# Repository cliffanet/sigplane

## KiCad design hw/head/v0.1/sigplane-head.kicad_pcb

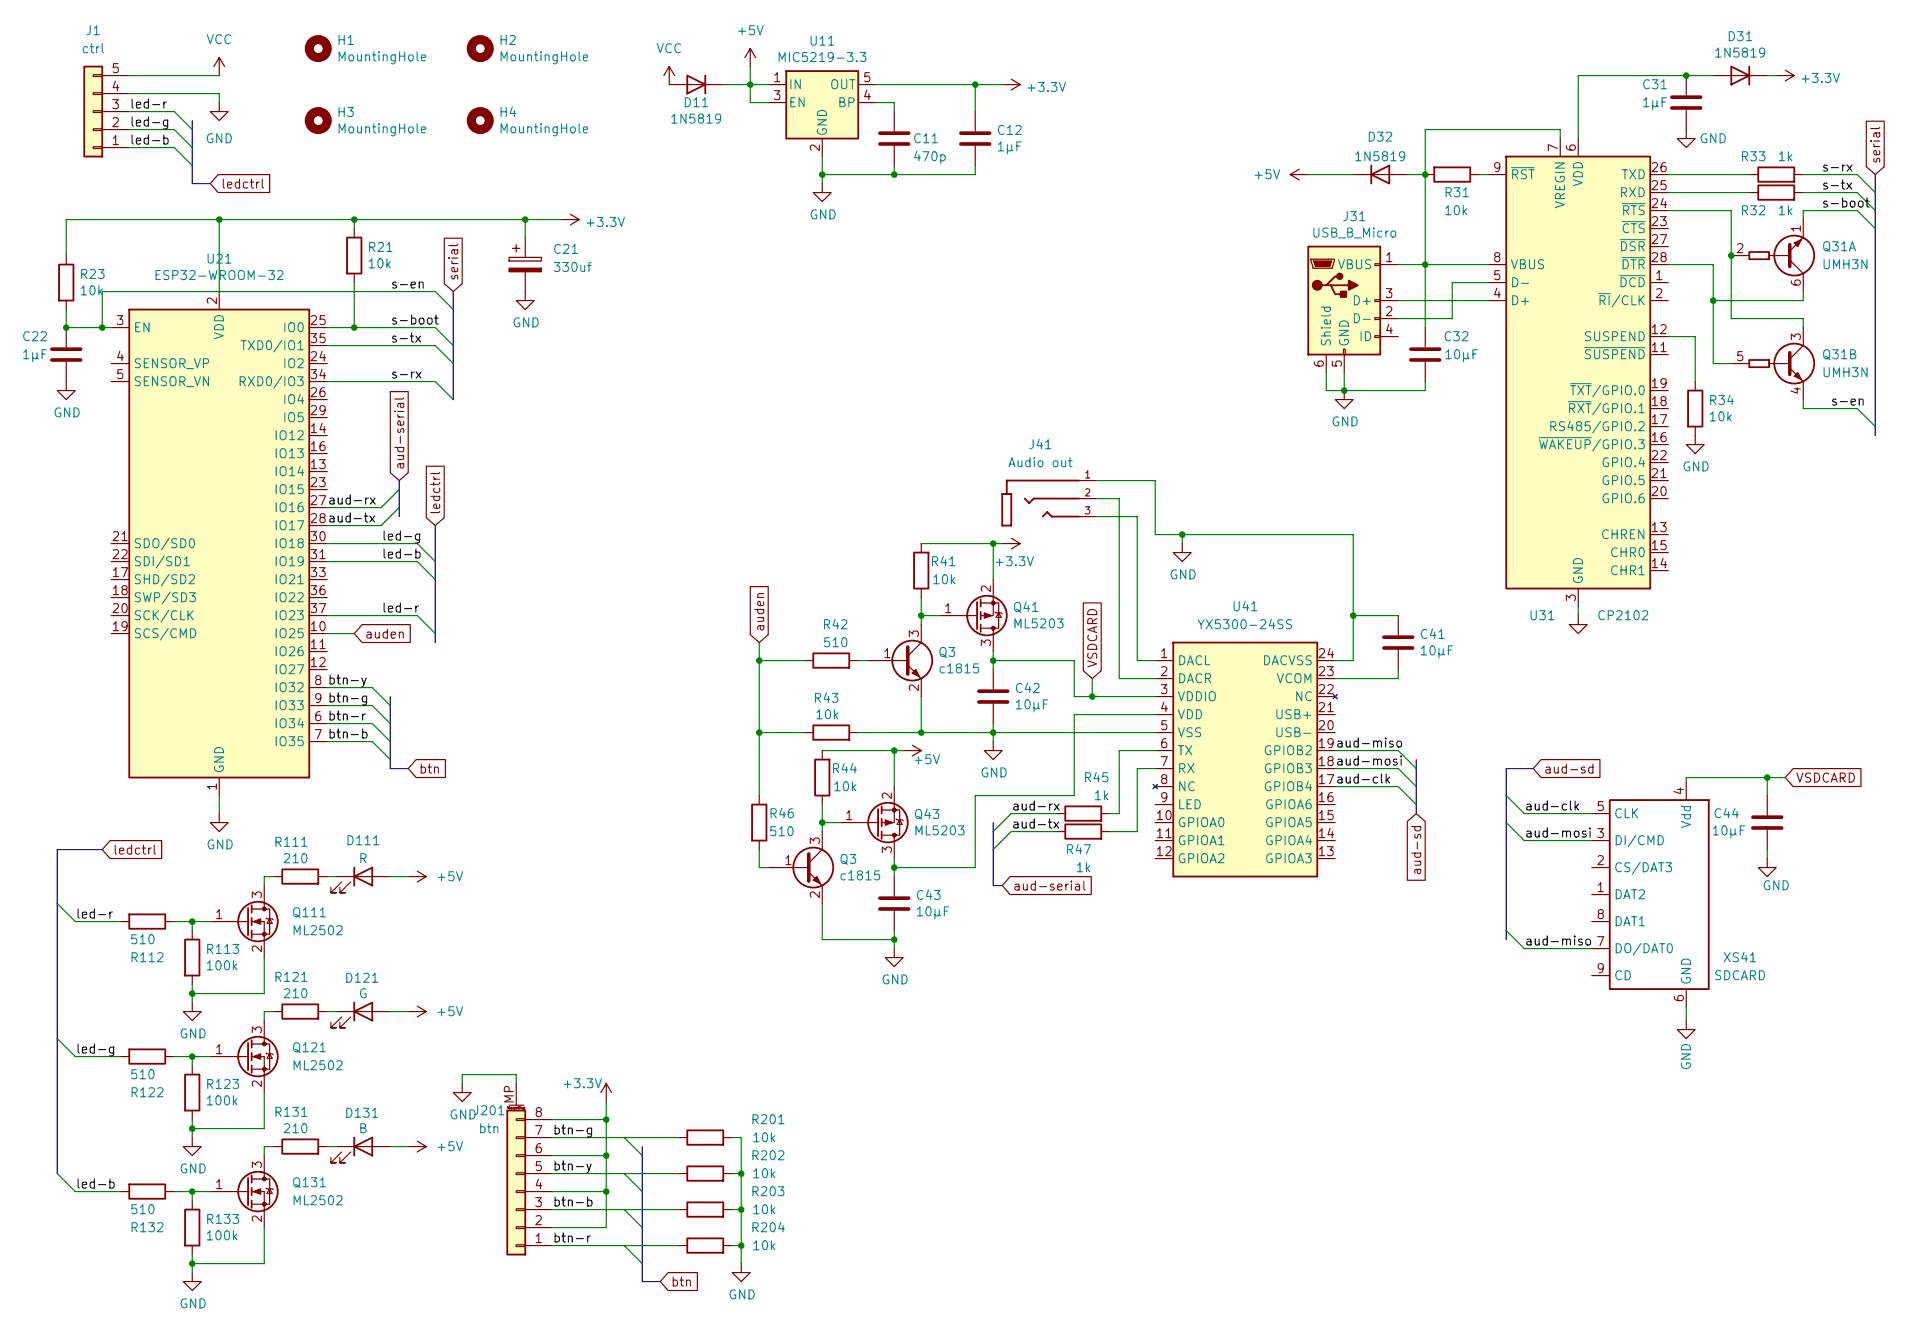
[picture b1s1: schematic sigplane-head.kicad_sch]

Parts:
C11: 470p; C_0805_2012Metric
C12, C22, C31: 1μF; C_0805_2012Metric
C21: 330uf; CP_EIA-7343-20_Kemet-V
C32, C41, C42, C43, C44: 10μF; C_0805_2012Metric
D11, D31, D32: 1N5819; D_SOD-323
D111: R; LED_D10.0mm
D121: G; LED_D10.0mm
D131: B; LED_D10.0mm
H1, H2, H3, H4: MountingHole; MountingHole_3.2mm_M3
J1: ctrl; JST_XH_S5B-XH-A_1x05_P2.50mm_Horizontal
J31: USB_B_Micro; USB_Micro-B_Molex-105017-0001
J41: Audio out; BOOMELE_PJ-320B
J201: btn; Molex_PicoBlade_53398-0871_1x08-1MP_P1.25mm_Vertical
Q3: c1815; SOT-23
Q31: UMH3N; SOT-363_SC-70-6
Q41, Q43: ML5203; SOT-23
Q111, Q121, Q131: ML2502; SOT-23
R21, R23, R31, R34, R41, R43, R44, R201, R202, R203, R204: 10k; R_0805_2012Metric
R32, R33, R45, R47: 1k; R_0805_2012Metric
R42, R46, R112, R122, R132: 510; R_0805_2012Metric
R111, R121, R131: 210; R_1206_3216Metric
R113, R123, R133: 100k; R_0805_2012Metric
U11: MIC5219-3.3; SOT-23-5
U21: ESP32-WROOM-32
U31: CP2102; QFN-28-1EP_5x5mm_P0.5mm_EP3.35x3.35mm
U41: YX5300-24SS; SSOP-24_3.9x8.7mm_P0.635mm
XS41: SDCARD; Conn_uSDcard

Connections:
+3.3V: C12.1, C21.1, D31.1 (K), J201.2, J201.4, J201.6, J201.8, Q41.2 (S), R21.1, R23.1, R41.2, U11.5 (OUT), U21.2 (VDD)
+5V: D11.1 (K), D32.1 (K), D111.2 (A), D121.2 (A), D131.2 (A), Q43.2 (S), R44.2, U11.1 (IN), U11.3 (EN)
/aud-clk: U41.17 (GPIOB4), XS41.5 (CLK)
/aud-miso: U41.19 (GPIOB2), XS41.7 (DO/DAT0)
/aud-mosi: U41.18 (GPIOB3), XS41.3 (DI/CMD)
/aud-rx: R45.1, U21.27 (IO16)
/aud-tx: R47.1, U21.28 (IO17)
/btn-b: J201.3, R203.1, U21.7 (IO35)
/btn-g: J201.7, R201.1, U21.9 (IO33)
/btn-r: J201.1, R204.1, U21.6 (IO34)
/btn-y: J201.5, R202.1, U21.8 (IO32)
/led-b: J1.1, R132.2, U21.31 (IO19)
/led-g: J1.2, R122.2, U21.30 (IO18)
/led-r: J1.3, R112.2, U21.37 (IO23)
/s-boot: Q31.1 (E1), R21.2, U21.25 (IO0)
/s-en: C22.1, Q31.4 (E2), R23.2, U21.3 (EN)
/s-rx: R33.2, U21.34 (RXD0/IO3)
/s-tx: R32.2, U21.35 (TXD0/IO1)
GND: C11.2, C12.2, C21.2, C22.2, C31.2, C32.1, C41.1, C42.2, C43.2, C44.2, J1.4, J31.5 (GND), J31.6 (Shield), J41.1, J201.MP (MountPin), Q111.2 (S), Q121.2 (S), Q131.2 (S), R34.2, R43.2, R113.2, R123.2, R133.2, R201.2, R202.2, R203.2, R204.2, U11.2 (GND), U21.1 (GND), U21.15 (GND), U21.38 (GND), U21.39 (GND), U31.3 (GND), U31.29 (GND), U41.5 (VSS), U41.24 (DACVSS), XS41.6 (GND); also elsewhere on the board
unnamed: C31.1, D31.2 (A), U31.6 (VDD)
unnamed: C32.2, D32.2 (A), J31.1 (VBUS), R31.2, U31.7 (VREGIN), U31.8 (VBUS)
unnamed: D111.1 (K), R111.2
unnamed: D121.1 (K), R121.2
unnamed: D131.1 (K), R131.2
unnamed: J31.3 (D+), U31.4 (D+)
unnamed: J31.2 (D-), U31.5 (D-)
unnamed: Q31.2 (B1), Q31.3 (C2), U31.24 (~RTS)
unnamed: Q31.5 (B2), Q31.6 (C1), U31.28 (~DTR)
unnamed 28: Q41.1 (G), R41.1; also elsewhere on the board
unnamed 29: R42.2; also elsewhere on the board
unnamed: C43.1, Q43.3 (D), U41.4 (VDD)
unnamed 31: Q43.1 (G), R44.1; also elsewhere on the board
unnamed 32: R46.2; also elsewhere on the board
unnamed: Q111.3 (D), R111.1
unnamed: Q111.1 (G), R112.1, R113.1
unnamed: Q121.3 (D), R121.1
unnamed: Q121.1 (G), R122.1, R123.1
unnamed: Q131.3 (D), R131.1
unnamed: Q131.1 (G), R132.1, R133.1
unnamed: C11.1, U11.4 (BP)
unnamed: R32.1, U31.25 (RXD)
unnamed: R34.1, U31.12 (SUSPEND)
unnamed: R33.1, U31.26 (TXD)
unnamed: R31.1, U31.9 (~RST)
unnamed: J41.3, U41.1 (DACL)
unnamed: J41.2, U41.2 (DACR)
unnamed: R47.2, U41.7 (RX)
unnamed: R45.2, U41.6 (TX)
unnamed: C41.2, U41.23 (VCOM)
VCC: D11.2 (A), J1.5
VSDCARD: C42.1, C44.1, Q41.3 (D), U41.3 (VDDIO), XS41.4 (Vdd)
auden: R42.1, R43.1, R46.1, U21.10 (IO25)

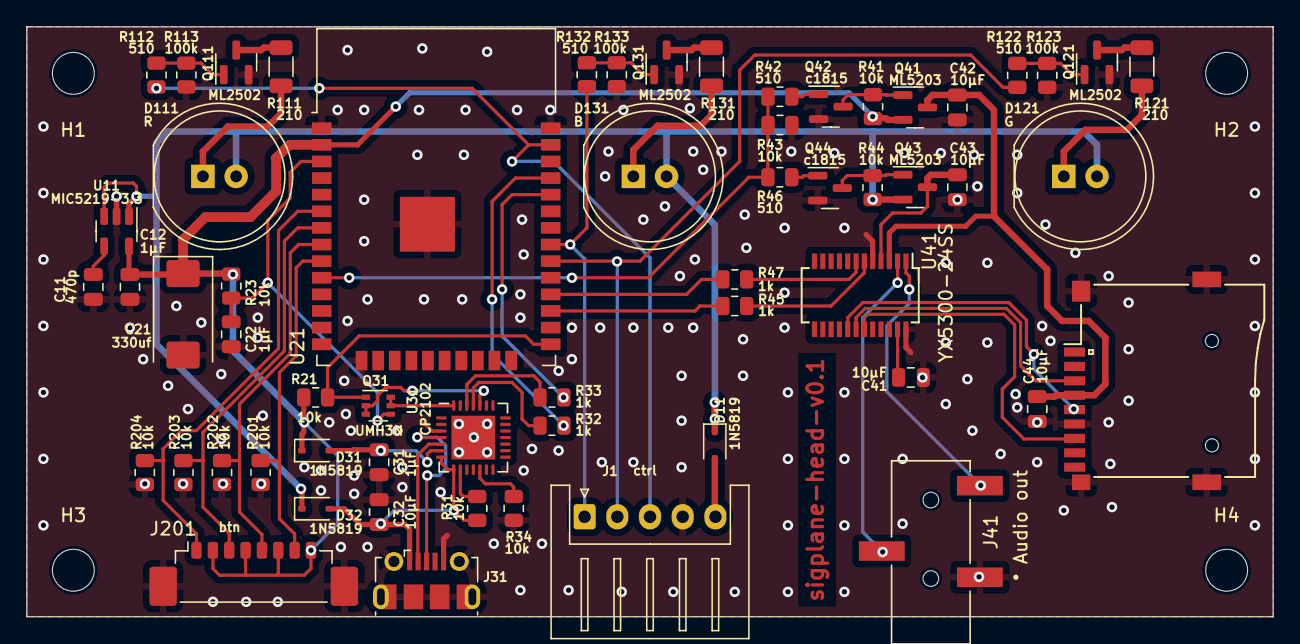
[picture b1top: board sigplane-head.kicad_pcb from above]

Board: 2 copper layers, 95.2 x 45.1 mm, 63 parts (0 on the bottom side), 52 nets.

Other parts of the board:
Q42, Q44: c1815; SOT-23

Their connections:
GND: Q42.2 (E), Q44.2 (E); also elsewhere on the board
unnamed 28: Q42.3 (C); also elsewhere on the board
unnamed 29: Q42.1 (B); also elsewhere on the board
unnamed 31: Q44.3 (C); also elsewhere on the board
unnamed 32: Q44.1 (B); also elsewhere on the board

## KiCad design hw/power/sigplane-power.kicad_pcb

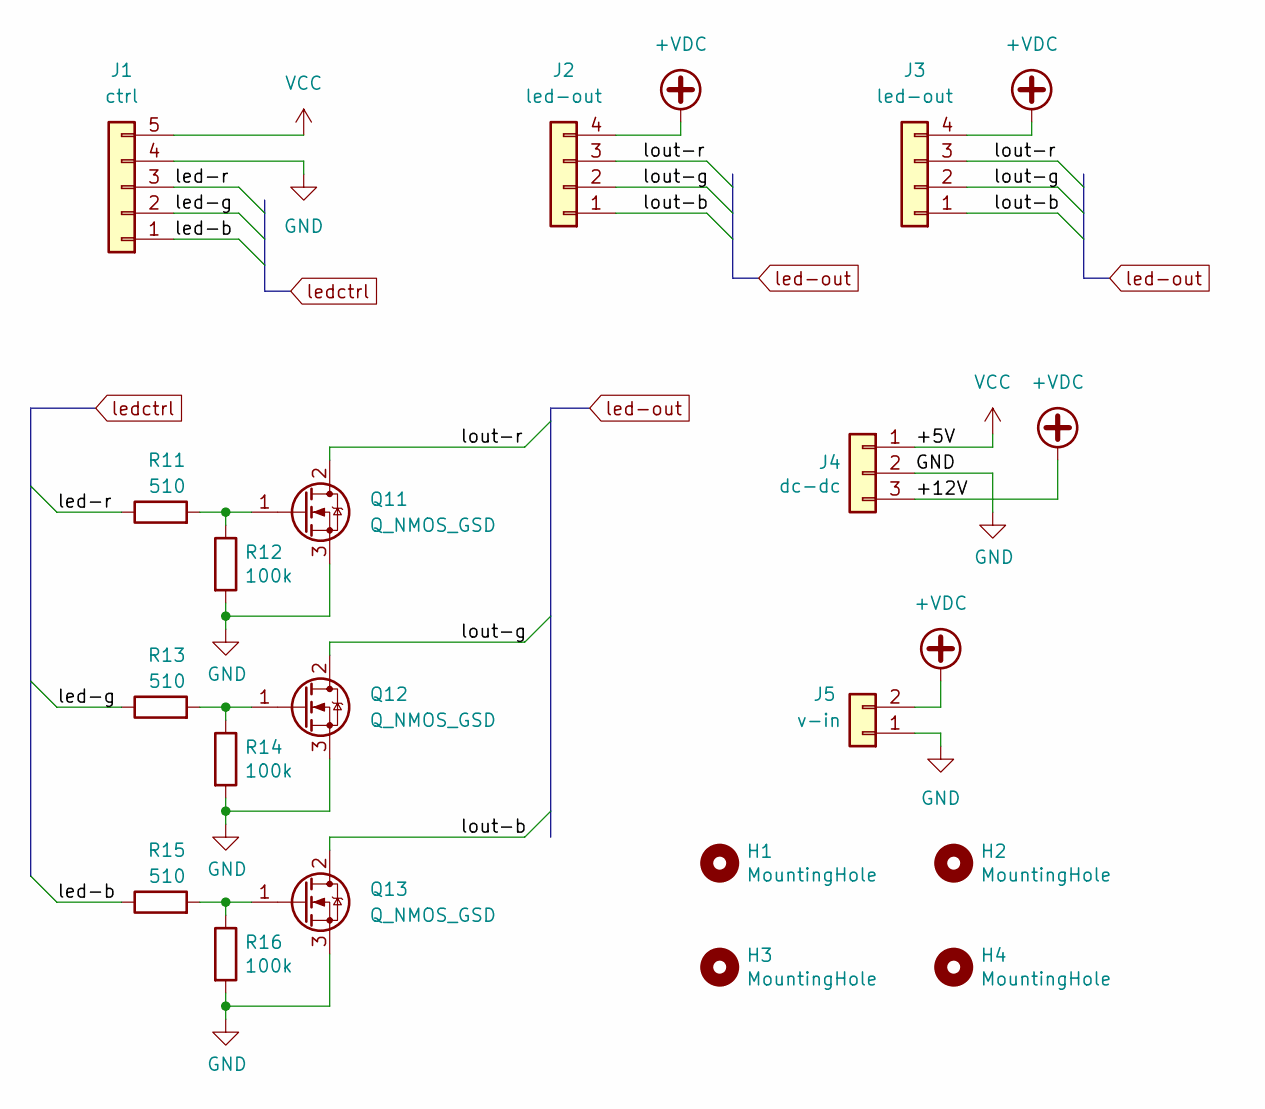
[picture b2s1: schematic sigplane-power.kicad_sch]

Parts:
H1, H2, H3, H4: MountingHole; MountingHole_3.2mm_M3
J1: ctrl; JST_XH_S5B-XH-A_1x05_P2.50mm_Horizontal
J2, J3: led-out; JST_XH_S4B-XH-A_1x04_P2.50mm_Horizontal
J4: dc-dc; PinHeader_1x03_P2.54mm_Vertical
J5: v-in; SolderWire-0.75sqmm_1x02_P4.8mm_D1.25mm_OD2.3mm
Q11, Q12, Q13: Q_NMOS_GSD; TO-263-2
R11, R13, R15: 510; R_0805_2012Metric
R12, R14, R16: 100k; R_0805_2012Metric

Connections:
+VDC: J2.4, J3.4, J4.3, J5.2
/led-b: J1.1, R15.1
/led-g: J1.2, R13.1
/led-r: J1.3, R11.1
/lout-b: J2.1, J3.1, Q13.2 (D)
/lout-g: J2.2, J3.2, Q12.2 (D)
/lout-r: J2.3, J3.3, Q11.2 (D)
GND: J1.4, J4.2, J5.1, Q11.3 (S), Q12.3 (S), Q13.3 (S), R12.2, R14.2, R16.2
unnamed: Q11.1 (G), R11.2, R12.1
unnamed: Q12.1 (G), R13.2, R14.1
unnamed: Q13.1 (G), R15.2, R16.1
VCC: J1.5, J4.1

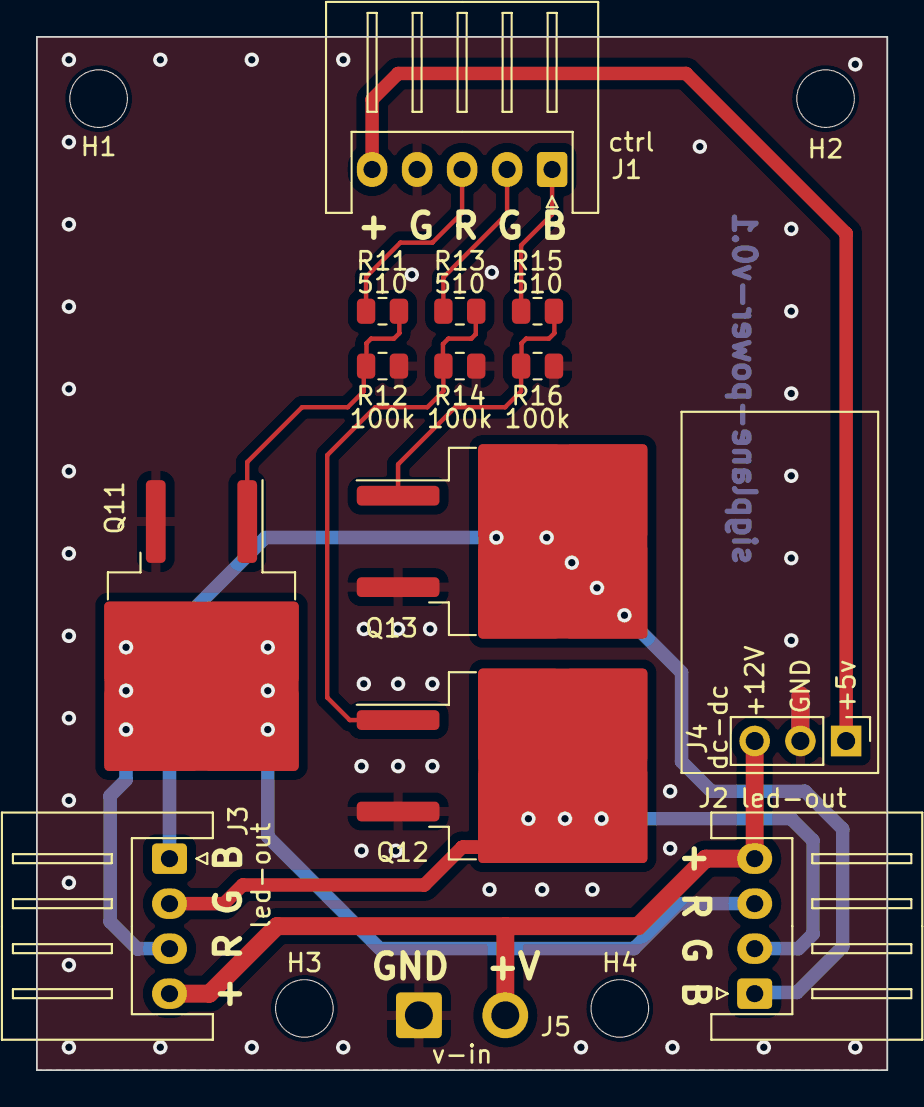
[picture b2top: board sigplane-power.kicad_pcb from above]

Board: 2 copper layers, 47.2 x 57.4 mm, 18 parts (0 on the bottom side), 12 nets.

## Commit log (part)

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2023-09-25 init
2023-09-25 таймаут на все сигналы
2023-10-07 платы - head только схема (требуется доработка), power - полностью с разводкой
2023-10-28 hw power - изменён корпус транзистора
2023-10-29 hw head - элементы размещены на плате, но не соединены
2023-10-29 hw head - плата разведена
2023-11-05 hw - гербер
2024-02-25 hw плата - поправлены косяки mp3-части
2024-02-25 воспроизведение mp3
2024-02-26 hw плата - небольшие доработки
2024-03-09 корпус обоих блоков
2024-03-09 удаляем старый пробный корпус
2024-05-20 переработан алгоритм работы с кнопками
2024-06-02 уменьшено время ожидания до 2 мин
